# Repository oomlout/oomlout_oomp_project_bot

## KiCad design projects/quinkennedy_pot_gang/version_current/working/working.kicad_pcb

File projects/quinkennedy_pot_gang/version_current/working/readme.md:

# pot-gang by quinkennedy  
This is a harvested standardized copy of a project from github.  
The original project can be found at:  
https://github.com/quinkennedy/pot-gang  
Please consult that link for additional, details, files, and license information.  
Note: It was auto harvested and if the original repo had more than one board file or anything out of the ordinary the files here are likely not representative.

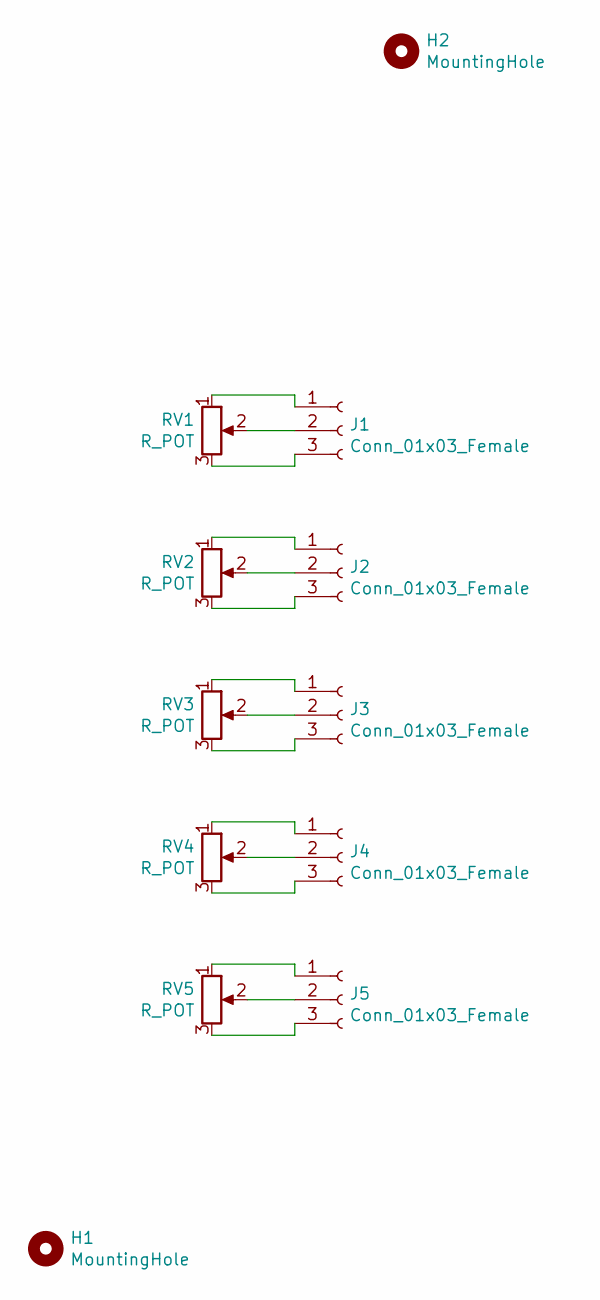
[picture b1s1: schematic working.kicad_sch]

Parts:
H1, H2: MountingHole; MountingHole_3.2mm_M3
J1, J2, J3, J4, J5: Conn_01x03_Female; PinHeader_1x03_P2.54mm_Vertical
RV1, RV2, RV3, RV4, RV5: R_POT; Potentiometer_Bourns_PTV09A-1_Single_Vertical

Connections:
unnamed: J1.1, RV1.1
unnamed: J1.2, RV1.2
unnamed: J1.3, RV1.3
unnamed: J2.1, RV2.1
unnamed: J2.2, RV2.2
unnamed: J2.3, RV2.3
unnamed: J3.1, RV3.1
unnamed: J3.2, RV3.2
unnamed: J3.3, RV3.3
unnamed: J4.1, RV4.1
unnamed: J4.2, RV4.2
unnamed: J4.3, RV4.3
unnamed: J5.1, RV5.1
unnamed: J5.2, RV5.2
unnamed: J5.3, RV5.3

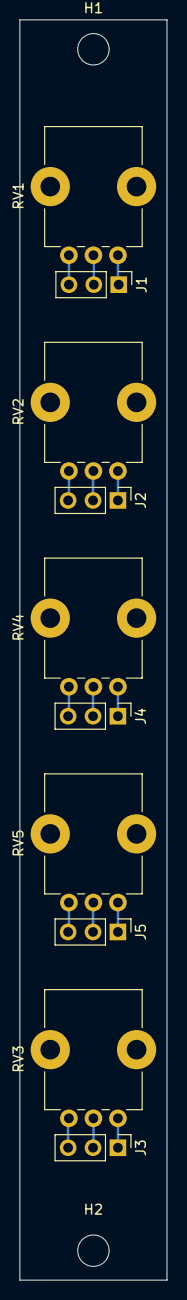
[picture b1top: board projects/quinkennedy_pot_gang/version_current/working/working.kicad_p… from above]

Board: 2 copper layers, 15.0 x 128.5 mm, 12 parts (0 on the bottom side), 15 nets.

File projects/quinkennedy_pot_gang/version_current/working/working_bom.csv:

"Id";"Designator";"Footprint";"Quantity";"Designation";"Supplier and ref";
1;"J1,J2,J3,J4,J5";"PinHeader_1x03_P2.54mm_Vertical";5;"Conn_01x03_Female";;;
2;"RV1,RV2,RV3,RV4,RV5";"Potentiometer_Bourns_PTV09A-1_Single_Vertical";5;"R_POT";;;

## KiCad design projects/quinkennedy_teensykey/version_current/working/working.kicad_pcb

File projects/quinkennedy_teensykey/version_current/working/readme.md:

# TeensyKey by quinkennedy  
This is a harvested standardized copy of a project from github.  
The original project can be found at:  
https://github.com/quinkennedy/TeensyKey  
Please consult that link for additional, details, files, and license information.  
Note: It was auto harvested and if the original repo had more than one board file or anything out of the ordinary the files here are likely not representative.

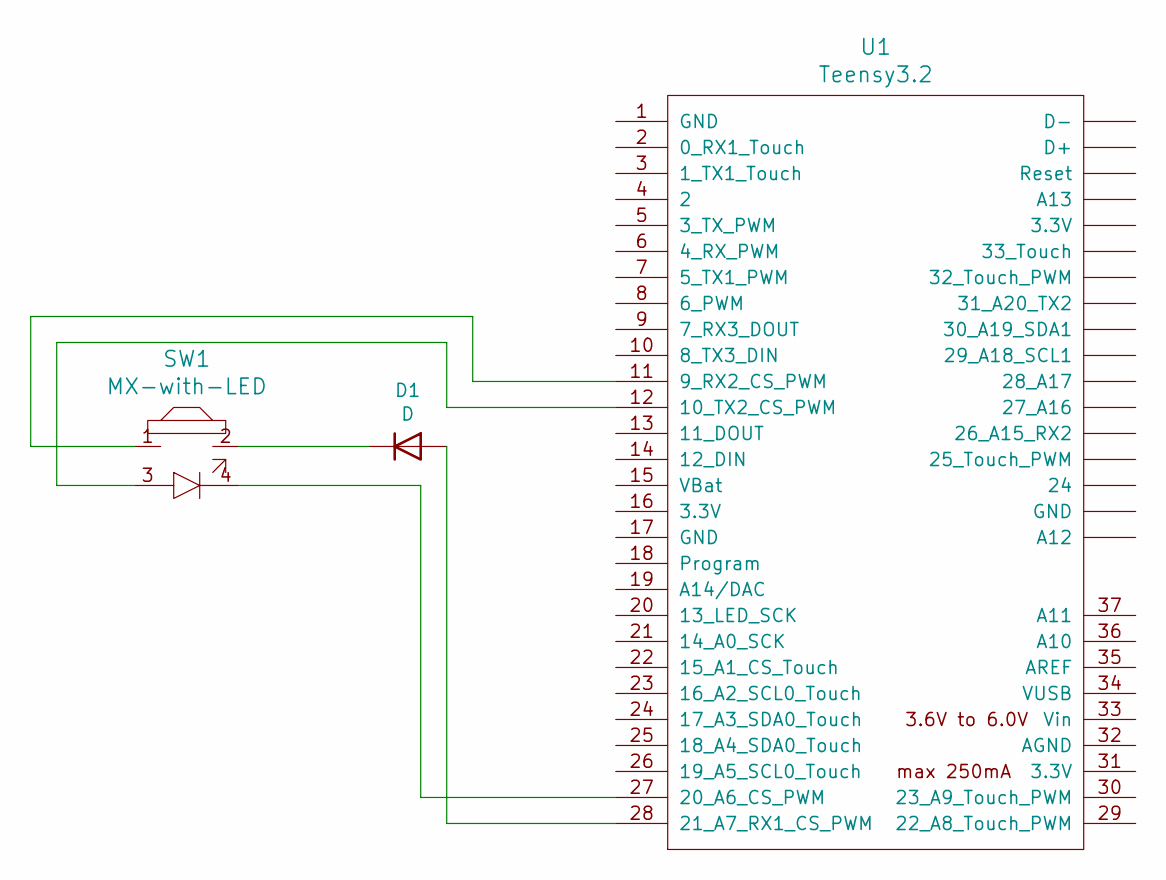
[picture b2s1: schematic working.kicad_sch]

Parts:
D1: D; D_DO-35_SOD27_P7.62mm_Horizontal
SW1: MX-with-LED; MX-Alps-Choc-1U
U1: Teensy3.2; Teensy30_31_32_LC_smt_combi

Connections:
unnamed: D1.1 (K), SW1.2
unnamed: D1.2 (A), U1.28 (21_A7_RX1_CS_PWM)
unnamed: SW1.1, U1.11 (9_RX2_CS_PWM)
unnamed: SW1.3, U1.12 (10_TX2_CS_PWM)
unnamed: SW1.4, U1.27 (20_A6_CS_PWM)

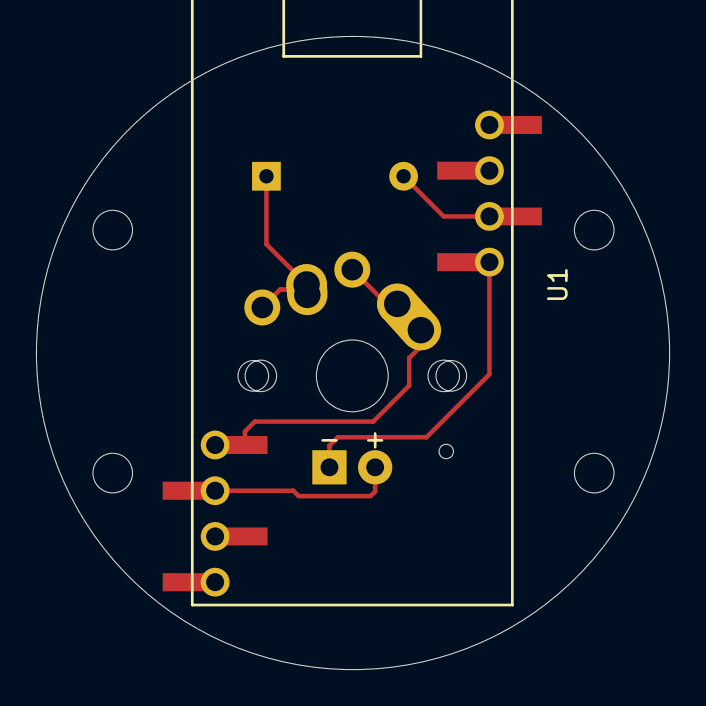
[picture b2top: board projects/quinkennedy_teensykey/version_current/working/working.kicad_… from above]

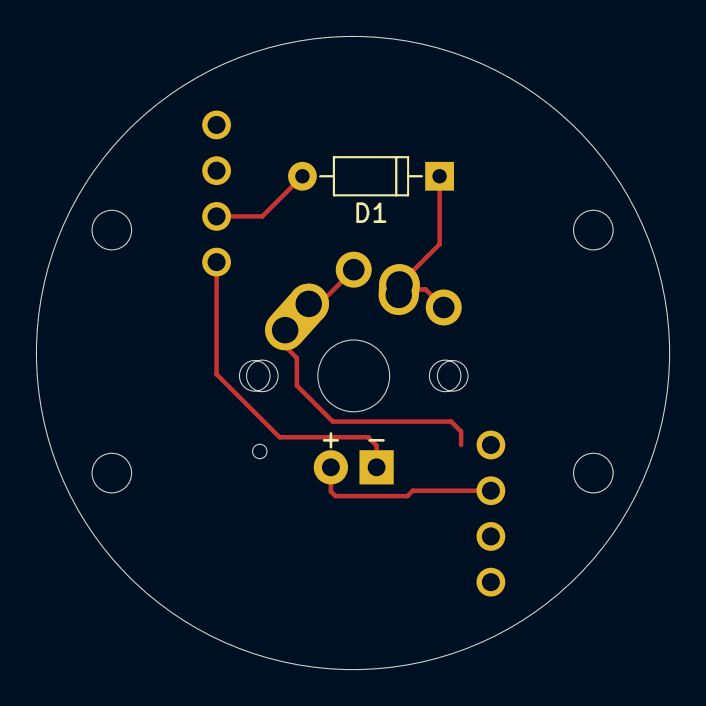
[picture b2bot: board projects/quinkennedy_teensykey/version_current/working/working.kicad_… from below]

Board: 2 copper layers, 35.2 x 35.2 mm, 3 parts (2 on the bottom side), 5 nets.

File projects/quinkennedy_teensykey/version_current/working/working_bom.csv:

"Id";"Designator";"Footprint";"Quantity";"Designation";"Supplier and ref";
1;"U1";"Teensy30_31_32_LC_smt_combi";1;"Teensy3.2";;;
2;"SW1";"MX-Alps-Choc-1U";1;"MX-with-LED";;;
3;"D1";"D_DO-35_SOD27_P7.62mm_Horizontal";1;"D";;;

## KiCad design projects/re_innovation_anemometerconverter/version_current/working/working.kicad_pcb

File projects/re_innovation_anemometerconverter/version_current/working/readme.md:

# AnemometerConverter by re-innovation  
This is a harvested standardized copy of a project from github.  
The original project can be found at:  
https://github.com/re-innovation/AnemometerConverter  
Please consult that link for additional, details, files, and license information.  
Note: It was auto harvested and if the original repo had more than one board file or anything out of the ordinary the files here are likely not representative.

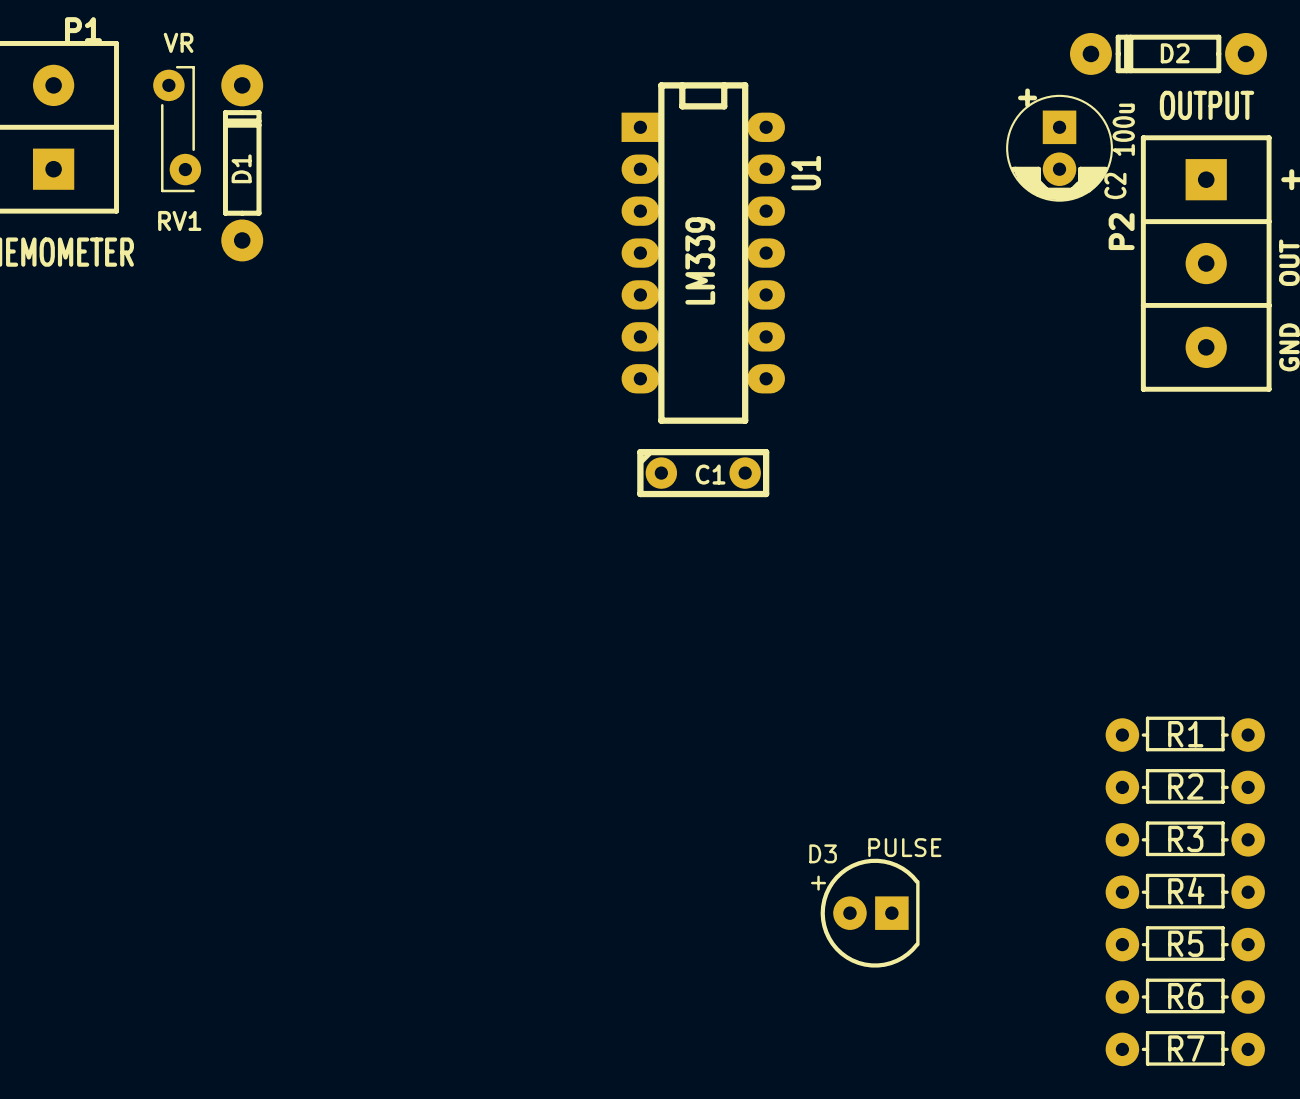
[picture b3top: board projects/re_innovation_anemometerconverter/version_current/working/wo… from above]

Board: 2 copper layers, 16 parts (0 on the bottom side), 9 nets, no tracks yet.

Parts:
C1: 22n; C1_wide_lg_pad
C2: 100u; C_1V7_TH
D1: 1N914; TH_Diode_1
D2: 1N4001; TH_Diode_1
D3: PULSE; TH_LED-5MM_larg_pad
P1: ANEMOMETER; SIL-2_screw_terminal
P2: OUTPUT; SIL-3_screw_terminal
R1, R2: 4k7; TH_Resistor_1
R3, R4: 100k; TH_Resistor_1
R5: 10k; TH_Resistor_1
R6: 4M7; TH_Resistor_1
R7: 1k; TH_Resistor_1
RV1: VR; TH_MC36188_FUSE
U1: LM339; DIP-14__300_ELL_lg_pad

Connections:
GND: C1.2, C2.2, D1.2, P1.1, P2.3, R5.2, R7.2, RV1.2, U1.12
unnamed: C1.1, R2.1, R3.2, U1.4
unnamed: D1.1, R1.1, R2.2
unnamed: D2.2, P2.1
unnamed: D3.1, R7.1
unnamed: D3.2, P2.2, R6.1, U1.2
unnamed: P1.2, R1.2, RV1.1
unnamed: R4.2, R5.1, R6.2, U1.5
VCC: C2.1, D2.1, R3.1, R4.1, U1.3

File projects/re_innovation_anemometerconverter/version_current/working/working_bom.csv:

"Id";"Designator";"Footprint";"Quantity";"Designation";"Supplier and ref";
1;"C1";"C1_wide_lg_pad";1;"22n";;;
2;"C2";"C_1V7_TH";1;"100u";;;
3;"D1";"TH_Diode_1";1;"1N914";;;
4;"D2";"TH_Diode_1";1;"1N4001";;;
5;"P1";"SIL-2_screw_terminal";1;"ANEMOMETER";;;
6;"P2";"SIL-3_screw_terminal";1;"OUTPUT";;;
7;"R1,R2";"TH_Resistor_1";2;"4k7";;;
8;"R3,R4";"TH_Resistor_1";2;"100k";;;
9;"R5";"TH_Resistor_1";1;"10k";;;
10;"R6";"TH_Resistor_1";1;"4M7";;;
11;"R7";"TH_Resistor_1";1;"1k";;;
12;"U1";"DIP-14__300_ELL_lg_pad";1;"LM339";;;
13;"RV1";"TH_MC36188_FUSE";1;"VR";;;

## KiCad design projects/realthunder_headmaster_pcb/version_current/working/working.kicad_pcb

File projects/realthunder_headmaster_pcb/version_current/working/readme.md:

# OOMP Project  
## headmaster_pcb  by realthunder  
  
oomp key: oomp_projects_flat_realthunder_headmaster_pcb  
(snippet of original readme)  

  full source readme at [readme_src.md](readme_src.md)  
  
source repo at: [https://github.com/realthunder/headmaster_pcb](https://github.com/realthunder/headmaster_pcb)  
## Board  

## Schematic  

[schematic pdf](working_schematic.pdf)  
## Images

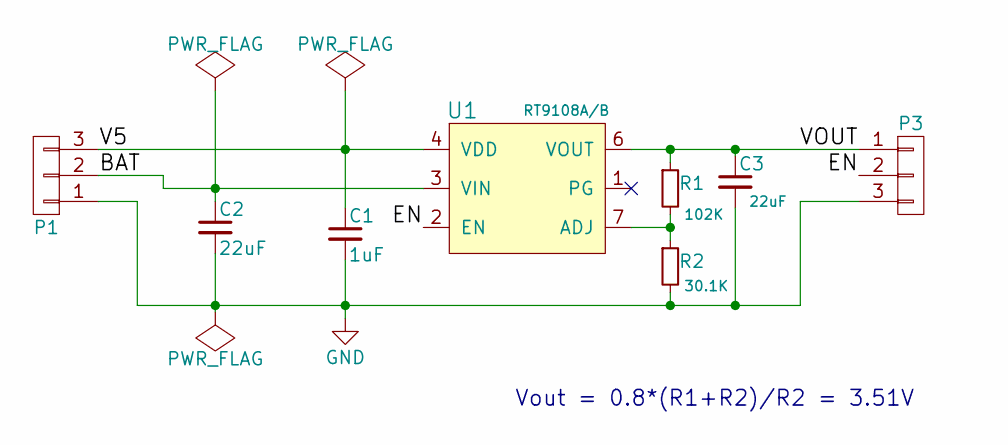
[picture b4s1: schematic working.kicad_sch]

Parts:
C1: 1uF; C_0402
C2, C3: 22uF; C_0805
P1, P3: CONN_01X01; Pin_Header_Straight_1x03
R1: 102K; R_0402
R2: 30.1K; R_0402
U1: RT9108A/B; SOIC-8-1EP_3.9x4.9mm_Pitch1.27mm

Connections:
/BAT: C2.1, P1.2, U1.3 (VIN)
/EN: P3.2, U1.2 (EN)
/V5: C1.1, P1.3, U1.4 (VDD)
/VOUT: C3.1, P3.1, R1.1, U1.6 (VOUT)
GND: C1.2, C2.2, C3.2, P1.1, P3.3, R2.2, U1.8 (GND), U1.9 (GND)
unnamed: R1.2, R2.1, U1.7 (ADJ)

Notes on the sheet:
Vout = 0.8*(R1+R2)/R2 = 3.51V

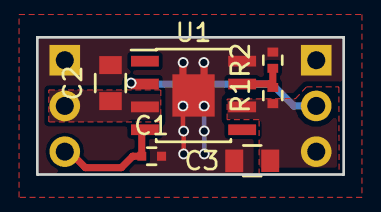
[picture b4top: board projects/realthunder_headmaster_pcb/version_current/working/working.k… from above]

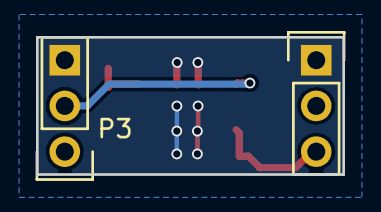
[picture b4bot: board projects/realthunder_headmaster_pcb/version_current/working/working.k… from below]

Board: 2 copper layers, 17.0 x 7.6 mm, 8 parts (2 on the bottom side), 6 nets.

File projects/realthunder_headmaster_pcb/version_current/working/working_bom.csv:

"Id";"Designator";"Footprint";"Quantity";"Designation";"Supplier and ref";
1;"C1";"C_0402";1;"1uF";;;
2;"C2,C3";"C_0805";2;"22uF";;;
3;"P3,P1";"Pin_Header_Straight_1x03";2;"CONN_01X01";;;
4;"R1";"R_0402";1;"102K";;;
5;"R2";"R_0402";1;"30.1K";;;
6;"U1";"SOIC-8-1EP_3.9x4.9mm_Pitch1.27mm";1;"RT9108A/B";;;

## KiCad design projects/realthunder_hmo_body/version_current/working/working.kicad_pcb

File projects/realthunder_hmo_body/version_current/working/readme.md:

# hmo_body by realthunder  
This is a harvested standardized copy of a project from github.  
The original project can be found at:  
https://github.com/realthunder/hmo_body  
Please consult that link for additional, details, files, and license information.  
Note: It was auto harvested and if the original repo had more than one board file or anything out of the ordinary the files here are likely not representative.

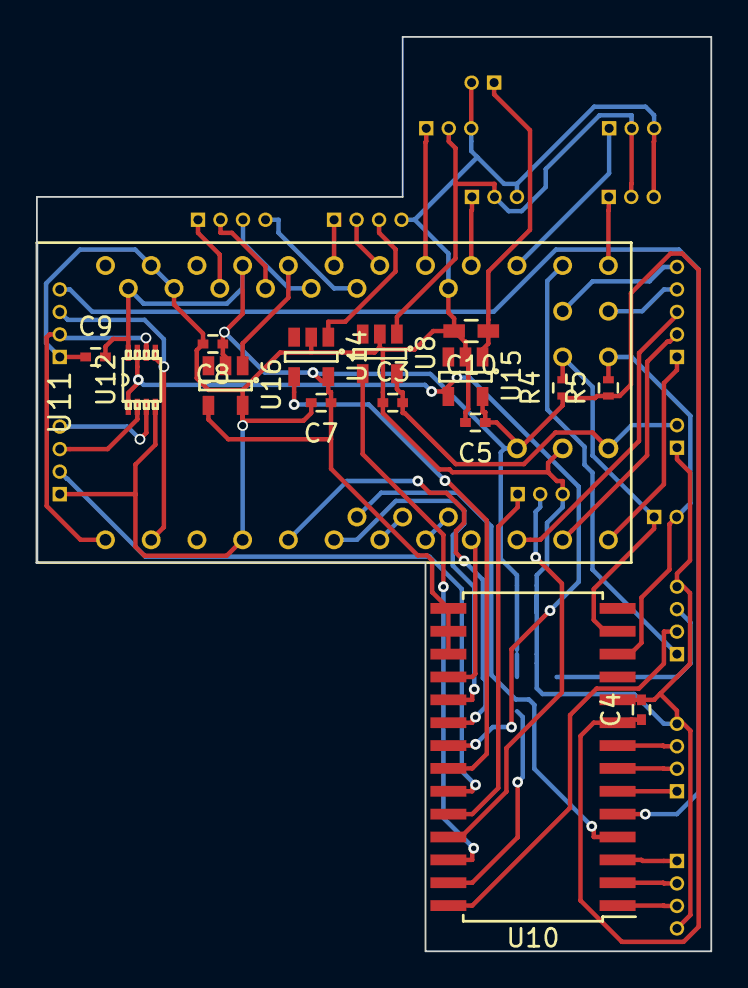
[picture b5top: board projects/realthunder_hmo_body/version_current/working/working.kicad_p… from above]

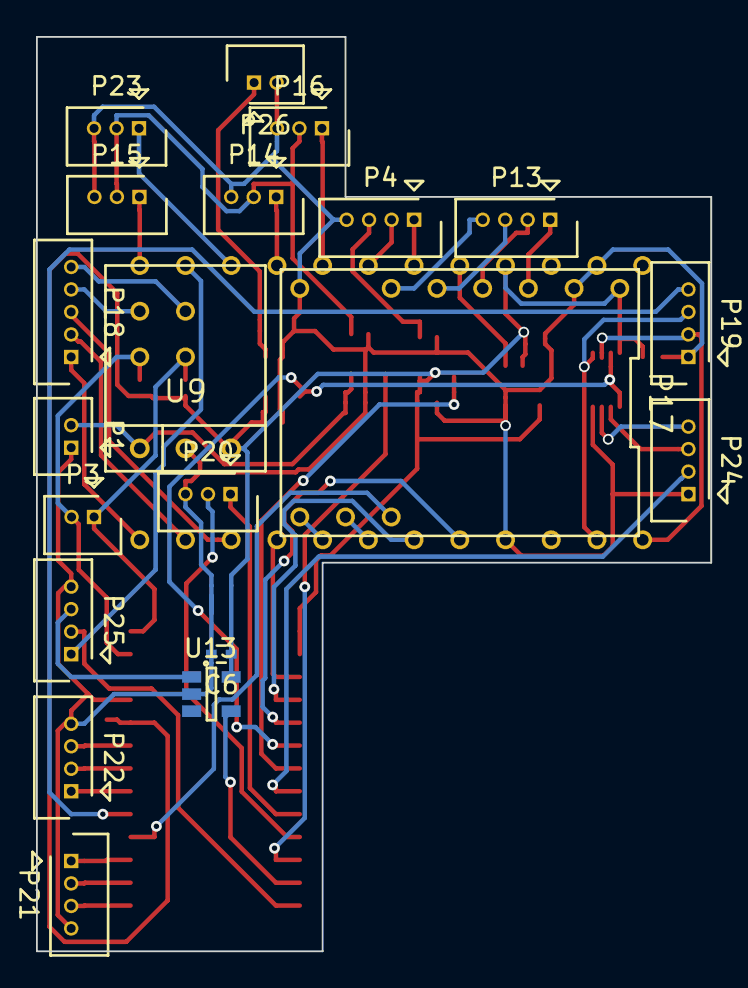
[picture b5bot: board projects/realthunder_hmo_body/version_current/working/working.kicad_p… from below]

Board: 2 copper layers, 37.5 x 50.8 mm, 36 parts (20 on the bottom side), 51 nets.

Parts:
C3, C5, C6, C7: 1uF; C_0402
C4, C8, C9: 0.1uF; C_0402
C10: 10uF; C_0603_HandSoldering
P1: CON_VIN; Molex_PicoBlade_53047-0210
P3: CON_I2C; Molex_PicoBlade_53047-0210
P4: CON_LED; Molex_PicoBlade_53047-0410
P13: CON_STEP; Molex_PicoBlade_53047-0410
P14: CON_SRV_CAM; Molex_PicoBlade_53047-0310
P15: CON_SRV_BRAKE; Molex_PicoBlade_53047-0310
P16: CON_SRV_LOCK; Molex_PicoBlade_53047-0310
P17: CON_POLOLU_DRV8834; POLOLU_DRV8834
P18: CON_BAT; Molex_PicoBlade_53047-0510
P19: CON_UART; Molex_PicoBlade_53047-0410
P20: CON_STEP_STOP; Molex_PicoBlade_53047-0310
P21: CON_BTN2; Molex_PicoBlade_53047-0410
P22: CON_BTN1; Molex_PicoBlade_53047-0410
P23: CON_SRV_FOOT; Molex_PicoBlade_53047-0310
P24: CON_EYEPIECE_COM; Molex_PicoBlade_53047-0410
P25: CON_FAN; Molex_PicoBlade_53047-0410
P26: CON_EP_VOUT; Molex_PicoBlade_53047-0210
R4, R5: 10K; R_0402
U8: SRV_SWITCH; SOT-23-5
U9: CON_POLOLU_PWR; POLOLU_U1V10F5
U10: MCP23017; SOIC-28W_7.5x17.9mm_Pitch1.27mm
U11: ProMini; PRO_MINI
U12: 74LVC2G126; TI_DCU_8
U13: FAN_SWITCH; SOT-23-5
U14: LED_SWITCH; SOT-23-5
U15: EP_SWITCH; SOT-23-5
U16: TMP36; SOT-23-5

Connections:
/BAT1_STAT: P18.2, U11.11
/BAT1_VOUT: P18.4, U11.31
/BAT2_STAT: P18.3, U11.10
/BAT2_VOUT: P18.5, U11.32
/BAT_CTL: P18.1, U11.12
/BTN11: P22.1, U10.6
/BTN12: P22.2, U10.7
/BTN13: P22.3, U10.8
/BTN21: P21.1, U10.3
/BTN22: P21.2, U10.2
/BTN23: P21.3, U10.1
/EP_EN: U10.21, U12.1, U12.7, U15.4
/EP_RXD: P24.4, U12.3
/EP_TXD: P24.3, U12.2
/EP_VOUT: C10.1, P26.1, U15.1
/FAN_EN: U10.27, U13.4
/FAN_PWM: P25.1, U11.14
/FAN_TACHO: P25.2, U10.28
/FAN_VOUT: P25.3, U13.1
/FRAME_STOP: P24.2, U10.23
/HOST_INT: P19.4, U10.5
/INTA: U10.20, U11.5
/INTB: U10.19, U11.6
/LED_CLK: P4.1, U11.19
/LED_DAT: P4.2, U11.18
/LED_EN: U10.22, U14.4
/LED_VOUT: P4.3, U14.1
/RXD: P19.3, U11.2, U12.5
/SCL: P3.2, R5.2, U10.12, U11.40
/SDA: P3.1, R4.2, U10.13, U11.39
/SRV_BRAKE: P15.1, U11.13
/SRV_CAM: P14.1, U11.16
/SRV_EN: U8.4, U10.26
/SRV_FOOT: P23.1, U11.15
/SRV_LOCK: P16.1, U11.17
/SRV_VOUT: P14.2, P15.2, P16.2, P23.2, U8.1
/STEP: P17.10, U11.7
/STEP_A1: P13.3, P17.5
/STEP_A2: P13.4, P17.6
/STEP_B1: P13.2, P17.4
/STEP_B2: P13.1, P17.3
/STEP_DIR: P17.9, U11.8
/STEP_STOP1: P20.1, U10.24
/STEP_STOP2: P20.2, U10.25
/TMP: U11.20, U16.1
/TXD: P19.2, U11.1, U12.6
/VIN: C3.2, P1.2, U8.5, U9.1
/~IO_RST: U10.18, U11.9
/~STEP_SLP: P17.11, U10.4
GND: C3.1, C4.2, C5.2, C6.2, C7.2, C8.2, C9.1, C10.2, P1.1, P4.4, P14.3, P15.3, P16.3, P17.2, P17.8, P19.1, P20.3, P21.4, P22.4, P23.3, P24.1, P25.4, P26.2, U8.2, U9.2, U10.10, U11.4, U11.23, U12.4, U13.2, U14.2, U15.2, U16.5
VCC: C4.1, C5.1, C6.1, C7.1, C8.1, C9.2, P17.1, R4.1, R5.1, U9.3, U10.9, U10.15, U10.16, U10.17, U11.21, U12.8, U13.5, U14.5, U15.5, U16.2, U16.4

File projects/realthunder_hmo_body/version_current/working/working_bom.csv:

"Id";"Designator";"Footprint";"Quantity";"Designation";"Supplier and ref";
1;"U11";"PRO_MINI";1;"ProMini";;;
2;"C3,C5,C6,C7";"C_0402";4;"1uF";;;
3;"C4,C8,C9";"C_0402";3;"0.1uF";;;
4;"P13";"Molex_PicoBlade_53047-0410";1;"CON_STEP";;;
5;"U8";"SOT-23-5";1;"SRV_SWITCH";;;
6;"C10";"C_0603_HandSoldering";1;"10uF";;;
7;"P14";"Molex_PicoBlade_53047-0310";1;"CON_SRV_CAM";;;
8;"P15";"Molex_PicoBlade_53047-0310";1;"CON_SRV_BRAKE";;;
9;"P16";"Molex_PicoBlade_53047-0310";1;"CON_SRV_LOCK";;;
10;"P19";"Molex_PicoBlade_53047-0410";1;"CON_UART";;;
11;"P23";"Molex_PicoBlade_53047-0310";1;"CON_SRV_FOOT";;;
12;"P24";"Molex_PicoBlade_53047-0410";1;"CON_EYEPIECE_COM";;;
13;"P26";"Molex_PicoBlade_53047-0210";1;"CON_EP_VOUT";;;
14;"R4,R5";"R_0402";2;"10K";;;
15;"U9";"POLOLU_U1V10F5";1;"CON_POLOLU_PWR";;;
16;"U10";"SOIC-28W_7.5x17.9mm_Pitch1.27mm";1;"MCP23017";;;
17;"U12";"TI_DCU_8";1;"74LVC2G126";;;
18;"U13";"SOT-23-5";1;"FAN_SWITCH";;;
19;"U14";"SOT-23-5";1;"LED_SWITCH";;;
20;"U15";"SOT-23-5";1;"EP_SWITCH";;;
21;"U16";"SOT-23-5";1;"TMP36";;;
22;"P18";"Molex_PicoBlade_53047-0510";1;"CON_BAT";;;
23;"P17";"POLOLU_DRV8834";1;"CON_POLOLU_DRV8834";;;
24;"P25";"Molex_PicoBlade_53047-0410";1;"CON_FAN";;;
25;"P1";"Molex_PicoBlade_53047-0210";1;"CON_VIN";;;
26;"P20";"Molex_PicoBlade_53047-0310";1;"CON_STEP_STOP";;;
27;"P3";"Molex_PicoBlade_53047-0210";1;"CON_I2C";;;
28;"P4";"Molex_PicoBlade_53047-0410";1;"CON_LED";;;
29;"P21";"Molex_PicoBlade_53047-0410";1;"CON_BTN2";;;
30;"P22";"Molex_PicoBlade_53047-0410";1;"CON_BTN1";;;

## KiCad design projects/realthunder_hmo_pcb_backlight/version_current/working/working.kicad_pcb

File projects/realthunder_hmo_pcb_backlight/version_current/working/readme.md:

# OOMP Project  
## hmo_pcb_backlight  by realthunder  
  
oomp key: oomp_projects_flat_realthunder_hmo_pcb_backlight  
(snippet of original readme)  

  full source readme at [readme_src.md](readme_src.md)  
  
source repo at: [https://github.com/realthunder/hmo_pcb_backlight](https://github.com/realthunder/hmo_pcb_backlight)  
## Board  

## Schematic  

[schematic pdf](working_schematic.pdf)  
## Images

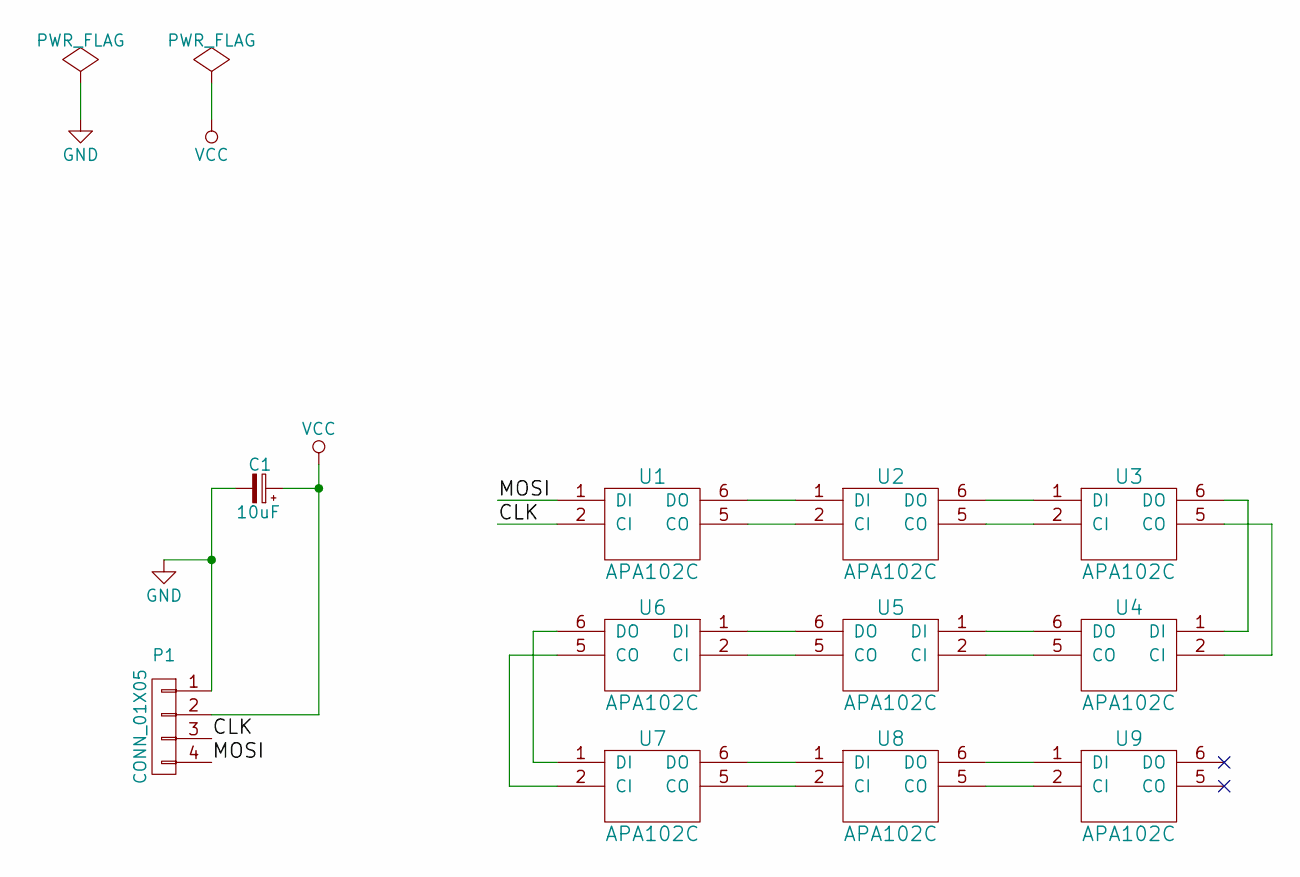
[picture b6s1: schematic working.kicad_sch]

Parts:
C1: 10uF; TantalC_SizeR_EIA-2012
P1: CONN_01X05; Molex_Panelmate-53780-0470_04x1.25mm_Angled
U1, U2, U3, U4, U5, U6, U7, U8, U9: APA102C

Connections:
/CLK: P1.3, U1.2 (CI)
/MOSI: P1.4, U1.1 (DI)
GND: C1.2, P1.1, U1.3 (GND), U2.3 (GND), U3.3 (GND), U4.3 (GND), U5.3 (GND), U6.3 (GND), U7.3 (GND), U8.3 (GND), U9.3 (GND)
unnamed: U1.5 (CO), U2.2 (CI)
unnamed: U1.6 (DO), U2.1 (DI)
unnamed: U2.5 (CO), U3.2 (CI)
unnamed: U2.6 (DO), U3.1 (DI)
unnamed: U3.5 (CO), U4.2 (CI)
unnamed: U3.6 (DO), U4.1 (DI)
unnamed: U4.5 (CO), U5.2 (CI)
unnamed: U4.6 (DO), U5.1 (DI)
unnamed: U5.5 (CO), U6.2 (CI)
unnamed: U5.6 (DO), U6.1 (DI)
unnamed: U6.5 (CO), U7.2 (CI)
unnamed: U6.6 (DO), U7.1 (DI)
unnamed: U7.5 (CO), U8.2 (CI)
unnamed: U7.6 (DO), U8.1 (DI)
unnamed: U8.5 (CO), U9.2 (CI)
unnamed: U8.6 (DO), U9.1 (DI)
VCC: C1.1, P1.2, U1.4 (VCC), U2.4 (VCC), U3.4 (VCC), U4.4 (VCC), U5.4 (VCC), U6.4 (VCC), U7.4 (VCC), U8.4 (VCC), U9.4 (VCC)

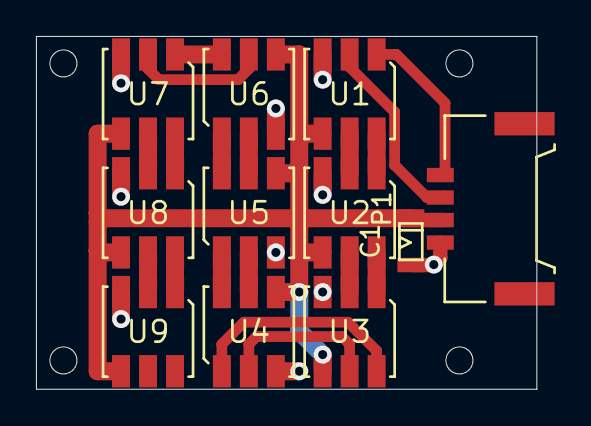
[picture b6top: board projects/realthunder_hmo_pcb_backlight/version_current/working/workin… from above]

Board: 2 copper layers, 27.8 x 19.6 mm, 11 parts (0 on the bottom side), 20 nets.

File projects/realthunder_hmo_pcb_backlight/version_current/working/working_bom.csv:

"Id";"Designator";"Footprint";"Quantity";"Designation";"Supplier and ref";
1;"C1";"TantalC_SizeR_EIA-2012";1;"10uF";;;
2;"REF**,REF**,REF**,REF**";"MountingHole_1.5mm";4;"MountingHole_2.5mm";;;
3;"U8,U7,U6,U5,U4,U3,U2,U1,U9";"APA102C";9;"APA102C";;;
4;"P1";"Molex_Panelmate-53780-0470_04x1.25mm_Angled";1;"CONN_01X05";;;

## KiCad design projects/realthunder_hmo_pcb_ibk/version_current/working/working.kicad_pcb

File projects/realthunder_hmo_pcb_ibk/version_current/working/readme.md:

# hmo_pcb_ibk by realthunder  
This is a harvested standardized copy of a project from github.  
The original project can be found at:  
https://github.com/realthunder/hmo_pcb_ibk  
Please consult that link for additional, details, files, and license information.  
Note: It was auto harvested and if the original repo had more than one board file or anything out of the ordinary the files here are likely not representative.

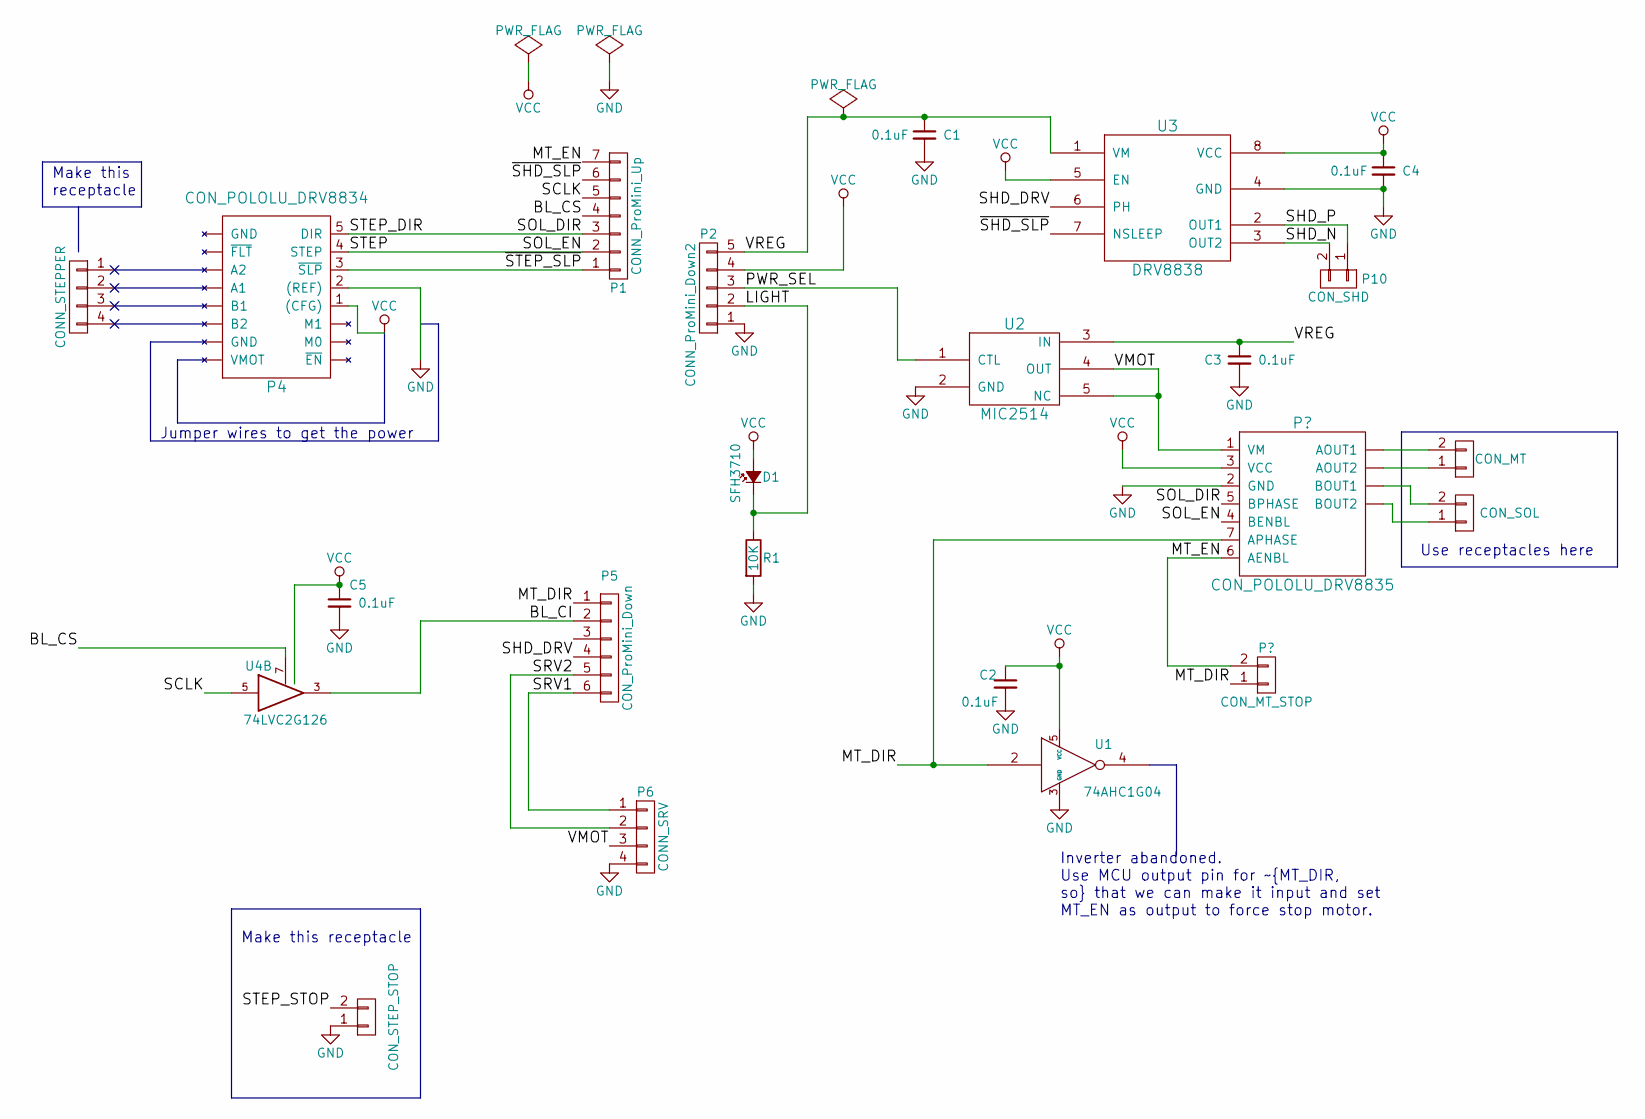
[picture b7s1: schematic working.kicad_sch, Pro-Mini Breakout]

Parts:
C1, C2, C3, C4, C5: 0.1uF; C_0402
D1: SFH3710; LED_0805
P1: CONN_ProMini_Up; Molex_PicoBlade_53261-0771
P2: CONN_ProMini_Down2; Molex_Panelmate-53780-0570_05x1.25mm_Angled
P4: CON_POLOLU_DRV8834; Pin_Header_Straight_1x05
P5: CON_ProMini_Down; Molex_Panelmate-53780-0670_06x1.25mm_Angled
P6: CONN_SRV; Molex_PicoBlade_53048-0410
P10: CON_SHD; Pin_Header_Straight_1x02_Pitch1.27mm
R1: 10K; R_0402
U1: 74AHC1G04; SOT-353
U2: MIC2514; SOT-23-5
U3: DRV8838; DRV8838_DSG_8
U4: 74LVC2G126; SN74LVC2G126_DCU_8

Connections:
/BL_CI: P5.2, U4.3
/BL_CS: P1.4, U4.1, U4.7
/BL_DO: P5.3, U4.2
/LIGHT: D1.1 (K), P2.2, R1.1
/MT_DIR: P5.1, U1.2; also elsewhere on the board
/MT_STOP: P1.7; also elsewhere on the board
/SCLK: P1.5, U4.5
/SHD_DRV: P5.4, U3.6 (PH)
/SHD_N: P10.2, U3.3 (OUT2)
/SHD_P: P10.1, U3.2 (OUT1)
/SOL_DIR: P1.3, P4.5 (DIR)
/SOL_EN: P1.2, P4.4 (STEP)
/SRV1: P5.6, P6.1
/SRV2: P5.5, P6.2
/VMOT: P6.3, U2.4 (OUT), U2.5 (NC); also elsewhere on the board
/VREG: C1.1, C3.1, P2.5, U2.3 (IN), U3.1 (VM)
/~STEP_SLP: P1.1, P4.3 (~SLP), U3.5 (EN)
GND: C1.2, C2.2, C3.2, C4.2, C5.2, P2.1, P4.2 ((REF)), P6.4, R1.2, U1.3 (GND), U2.2 (GND), U3.4 (GND), U3.9, U4.4 (GND); also elsewhere on the board
unnamed 18: U1.4; also elsewhere on the board
VCC: C2.1, C4.1, C5.1, D1.2 (A), P2.4, P4.1 ((CFG)), U1.5 (VCC), U3.8 (VCC), U4.8 (VCC); also elsewhere on the board

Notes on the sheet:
Inverter abandoned. Use MCU output pin for ~{MT_DIR, so} that we can make it input and set MT_EN as output to force stop motor.
Use receptacles here
Make this receptacle
Jumper wires to get the power
Make this receptacle

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
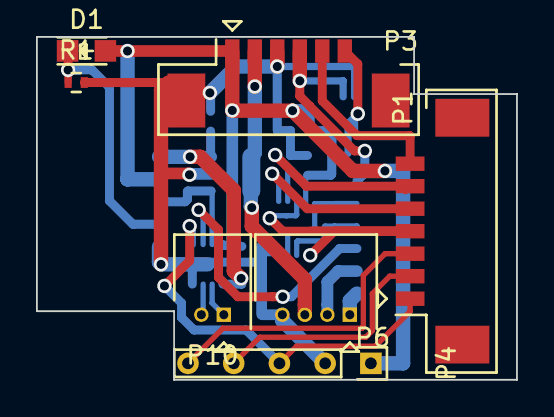
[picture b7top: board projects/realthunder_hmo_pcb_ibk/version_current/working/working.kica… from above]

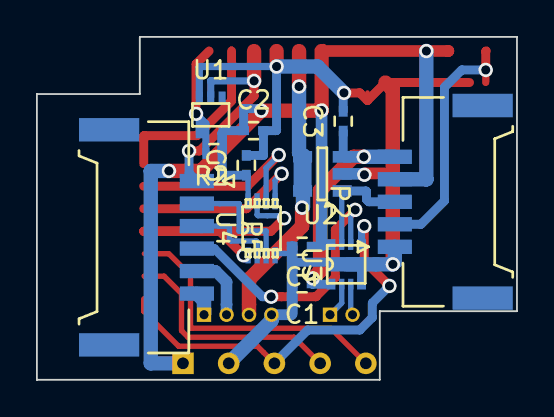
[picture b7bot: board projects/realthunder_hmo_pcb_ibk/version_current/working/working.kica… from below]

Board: 2 copper layers, 26.7 x 19.1 mm, 20 parts (13 on the bottom side), 22 nets.

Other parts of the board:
P3: CON_MT; Molex_PicoBlade_53398-0671
R2: 10K; R_0402
__P2: Molex_Panelmate-51146-0500

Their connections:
/MT_DIR: P3.4; also elsewhere on the board
/MT_STOP: P3.5; also elsewhere on the board
/VMOT: P3.2; also elsewhere on the board
GND: P3.3; also elsewhere on the board
unnamed 18: P3.6, R2.2; also elsewhere on the board
VCC: P3.1, R2.1; also elsewhere on the board

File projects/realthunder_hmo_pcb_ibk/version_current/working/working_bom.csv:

"Id";"Designator";"Footprint";"Quantity";"Designation";"Supplier and ref";
1;"P10";"Molex_PicoBlade_53048-0210";1;"CON_SHD";;;
2;"R1,R2";"R_0402";2;"10K";;;
3;"U2";"SOT-23-5";1;"MIC2514";;;
4;"C5,C4,C3,C2,C1";"C_0402";5;"0.1uF";;;
5;"D1";"LED_0805";1;"SFH3710";;;
6;"P6";"Molex_PicoBlade_53048-0410";1;"CONN_SRV";;;
7;"P4";"Pin_Header_Straight_1x05";1;"CON_POLOLU_DRV8834";;;
8;"P2";"Molex_Panelmate-53780-0570_05x1.25mm_Angled";1;"CONN_ProMini_Down2";;;
9;"P5";"Molex_Panelmate-53780-0670_06x1.25mm_Angled";1;"CON_ProMini_Down";;;
10;"REF**";"Molex_PicoBlade_51021-53048-0410";1;"Molex_PicoBlade_51021-0400";;;
11;"P1";"Molex_PicoBlade_53261-0771";1;"CONN_ProMini_Up";;;
12;"P3";"Molex_PicoBlade_53398-0671";1;"CON_MT";;;
13;"REF**";"Molex_PicoBlade_51021-53261-0771";1;"Molex_PicoBlade_51021-0700";;;
14;"REF**";"Molex_PicoBlade_51021-53261-0671";1;"Molex_PicoBlade_51021-0600";;;
15;"REF**";"Molex_Panelmate-51146-0600";1;"Molex_Panelmate-51146-0600";;;
16;"__P2";"Molex_Panelmate-51146-0500";1;"Molex_Panelmate-51146-0500";;;
17;"U3";"DRV8838_DSG_8_ManualSolder";1;"DRV8838";;;
18;"U1";"SOT-353";1;"74AHC1G04";;;
19;"U4";"SN74LVC2G126_DCU_8";1;"74LVC2G126";;;

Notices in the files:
parts and their libraries:
Copyright 2016 Accelerated Designs. All rights reserved.
